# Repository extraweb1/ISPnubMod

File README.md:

# ISPnubMod

Firmware for stand-alone AVR programmer module.

ISPnub is a stand-alone AVR programming module. The programming instructions
are defined within scripts. These scripts are converted with an additional
tool (ISPnubCreator) into a binary format and are stored in the flash of
ISPnub's ATmega1284P. This firmware interprets the binary programming
instructions and executes it on the connected target controller.
 
The firmware hex file is packed into the JAR file of ISPnubCreator which
merges the firmware hex data with programming instructions from scripts.

## Hardware / Boards

There are two dedicated boards to build the ISPnub. The original board is very small, further information you can get at the inventor of the <a href="http://www.fischl.de/ispnub/">original ISPnub</a>. The modded board <a href="https://oshpark.com/shared_projects/0ZfQJilI">can be ordered e.g. from OSHpark</a> and has some extra features on it:
  * Supported AVRs: ATmega1284, ATmega644, ATmega328@16MHz (Arduino Uno), ATmega32/16 (still untested)
  * 2 Power-Connectors
  * Buzzer
  * Connector for ISP 6-Header, Clamp and DIP-Socket
  * Internal vias for connecting a custom ISP-Header
  * Yellow LED for active programming state so the red one is used exclusively to display errors
  * Possibility to add a power switch (or just use a jumper)
  * 2 PINs breaked out for additional auxiliaries
Eagle files like schematics are to be found in 

If you would like to test the system on Arduino Uno first here is a connection diagram. Please be aware that the ISPnub-software only works if flashing the Arduino via ISP directly omitting the bootloader.

## Set up the Software / Usage

Detailed explanation about function and usage of the ISPnub are to be found at <a href="http://www.fischl.de/ispnub/">fischl.de</a>

In short:

### 1. Write a programming script (test.ispnub):
```
CONNECT 2000000                           ; connect with SCK = 2 MHz 
SPIVERIFY 0x30, 0x00, 0x00, 0x00, 0x1E    ; check signature byte 0x00 (0x1E = manufactured by Atmel)
SPIVERIFY 0x30, 0x00, 0x01, 0x00, 0x93    ; check signature byte 0x01 (0x93 = 8KB Flash memory)
SPIVERIFY 0x30, 0x00, 0x02, 0x00, 0x07    ; check signature byte 0x02 (0x07 = ATmega8 device)
SPIWRITE  0xAC, 0x80, 0x00, 0x00          ; chip erase
WAIT 2                                    ; wait 20 ms
FLASH ../test/main.hex, 0, 64             ; flash given hex file starting at flash address 0 with pagesize 64
DISCONNECT                                ; disconnect SPI
DECCOUNTER 10                             ; allow 10 programming cycles
END
```
### 2. Build ISPnub firmware:
Take the java tool  to build the firmware to be flashed to the ISPnub/Arduino.
Build the firmware like this for Arduino:
```
java -jar ISPnubCreator.jar test.ispnub atmega328_16MHz ispnub.hex
```

To use the modded firmware in compatibility-mode on the original ISPnub board execute:
```
java -jar ISPnubCreator.jar test.ispnub atmega1284_compat ispnub.hex
```

Or choose one of the other supported AVR in combination with the modded board:
```
java -jar ISPnubCreator.jar test.ispnub [atmega1284|atmega1284_compat|atmega328_16MHz|atmega16|atmega32|atmega644] ispnub.hex
```

### 3. Flash the ISPnub/Arduino:
Now the generated "ispnub.hex" can be flashed with your favorite programmer into the arduino. Take care for setting the fuses right. A working suggestion is given on the commandline by the java tool after building the firmware in step 2.

### 4. Flash targets by hitting the switch on the ISPnub

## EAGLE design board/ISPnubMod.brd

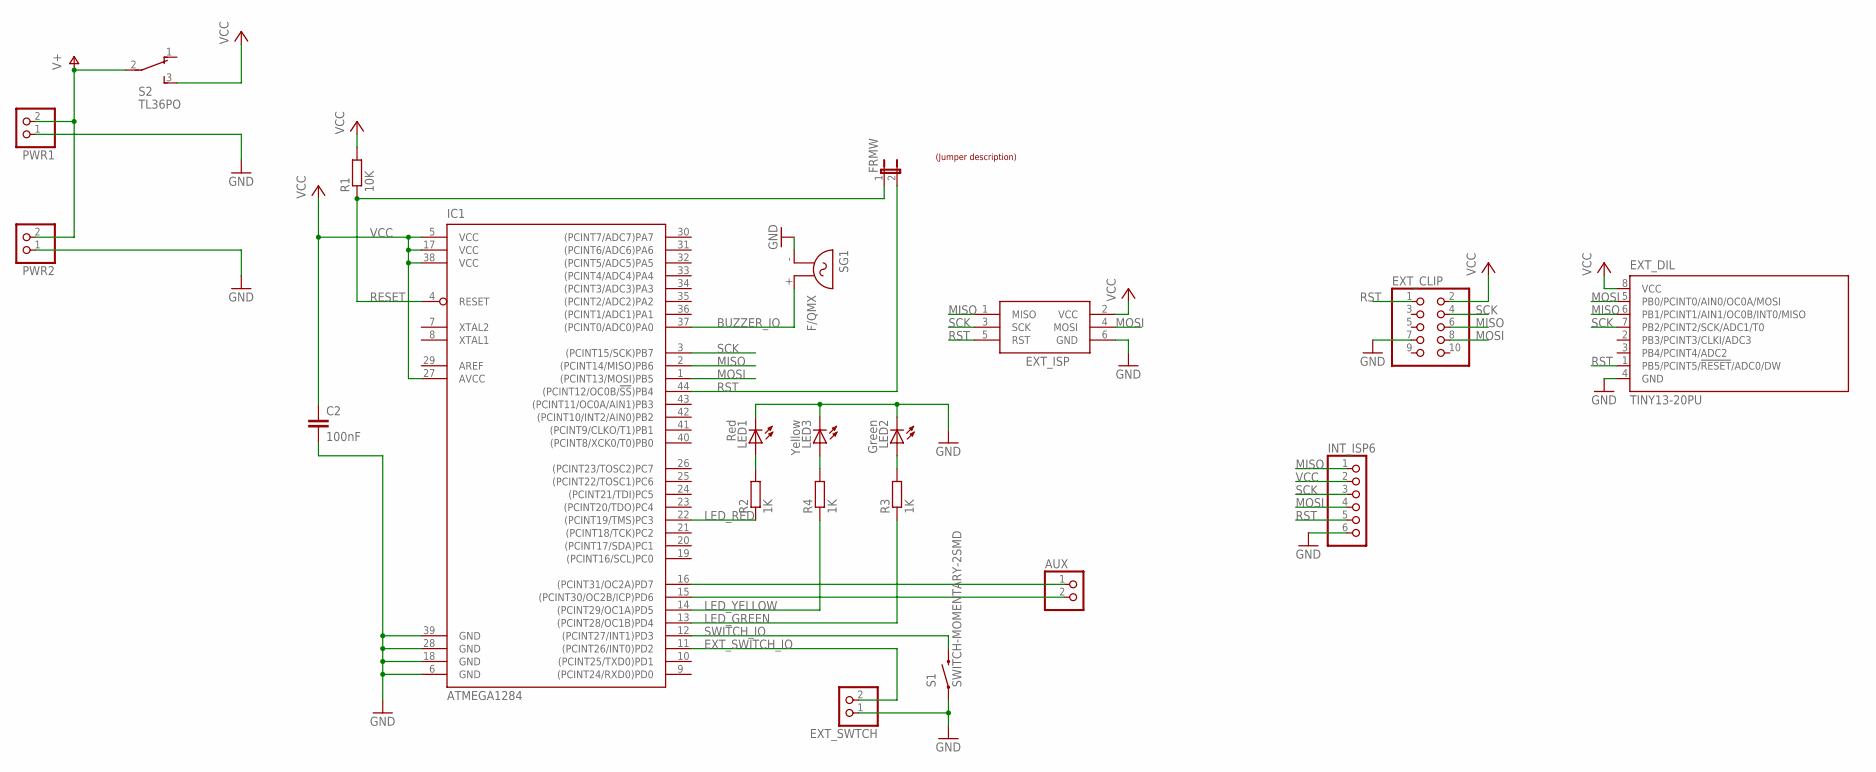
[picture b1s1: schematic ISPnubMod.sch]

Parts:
AUX: PINHD-1X2; 1X02
C2: 100nF; C0805; MOUSER# 80-C0805C104K5R
EXT_CLIP: PINHD-2X5; 2X05
EXT_DIL: TINY13-20PU; DIL08
EXT_ISP: AVRISP-6; AVRISP
EXT_SWTCH: PINHD-1X2; 1X02
FRMW: JP1E; JP1; MOUSER# 571-826936-2
IC1: ATMEGA1284; TQFP44; MOUSER# 556-ATMEGA1284P-AU
INT_ISP6: PINHD-1X6; 1X06
LED1: Red; CHIP-LED0805; MOUSER# 604-APT1608SURC
LED2: Green; CHIP-LED0805; MOUSER# 604-APT2012SGC
LED3: Yellow; CHIP-LED0805; MOUSER# 604-APT2012SGC
PWR1, PWR2: PINHD-1X2; 1X02
R1: 10K; R0805; MOUSER# 603-SR0805JR-0710KL
R2, R3, R4: 1K; R0805; MOUSER# 71-CRCW0805-1.0K-E3
S1: SWITCH-MOMENTARY-2SMD; TACTILE_SWITCH_SMD; MOUSER# 693-1301.9314
S2: TL36PO; TL3XPO
SG1: F/QMX
U$1: LABEL_JUMPER_1X2; JUMP2_DESC

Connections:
BUZZER_IO: IC1.37 ((PCINT0/ADC0)PA0), SG1.+ (2)
EXT_SWITCH_IO: EXT_SWTCH.2, IC1.11 ((PCINT26/INT0)PD2)
GND: C2.2, EXT_CLIP.7, EXT_DIL.4 (GND), EXT_ISP.6 (GND), EXT_SWTCH.1, IC1.6 (GND), IC1.18 (GND), IC1.28 (GND), IC1.39 (GND), INT_ISP6.6, LED1.C, LED2.C, LED3.C, PWR1.1, PWR2.1, S1.1, SG1.- (1)
LED_GREEN: IC1.13 ((PCINT28/OC1B)PD4), R3.1
LED_RED: IC1.22 ((PCINT19/TMS)PC3), R2.1
LED_YELLOW: IC1.14 ((PCINT29/OC1A)PD5), R4.1
MISO: EXT_CLIP.6, EXT_DIL.6 (PB1/PCINT1/AIN1/OC0B/INT0/MISO), EXT_ISP.1 (MISO), IC1.2 ((PCINT14/MISO)PB6), INT_ISP6.1
MOSI: EXT_CLIP.8, EXT_DIL.5 (PB0/PCINT0/AIN0/OC0A/MOSI), EXT_ISP.4 (MOSI), IC1.1 ((PCINT13/MOSI)PB5), INT_ISP6.4
unnamed: LED1.A, R2.2
unnamed: LED2.A, R3.2
unnamed: LED3.A, R4.2
PD6: AUX.2, IC1.15 ((PCINT30/OC2B/ICP)PD6)
PD7: AUX.1, IC1.16 ((PCINT31/OC2A)PD7)
RESET: FRMW.1, IC1.4 (RESET), R1.1
RST: EXT_CLIP.1, EXT_DIL.1 (PB5/PCINT5/!RESET!/ADC0/DW), EXT_ISP.5 (RST), FRMW.2, IC1.44 ((PCINT12/OC0B/!SS!)PB4), INT_ISP6.5
SCK: EXT_CLIP.4, EXT_DIL.7 (PB2/PCINT2/SCK/ADC1/T0), EXT_ISP.3 (SCK), IC1.3 ((PCINT15/SCK)PB7), INT_ISP6.3
SWITCH_IO: IC1.12 ((PCINT27/INT1)PD3), S1.3 (2)
V+: PWR1.2, PWR2.2, S2.2
VCC: C2.1, EXT_CLIP.2, EXT_DIL.8 (VCC), EXT_ISP.2 (VCC), IC1.5 (VCC), IC1.17 (VCC), IC1.27 (AVCC), IC1.38 (VCC), INT_ISP6.2, R1.2, S2.3 (S)

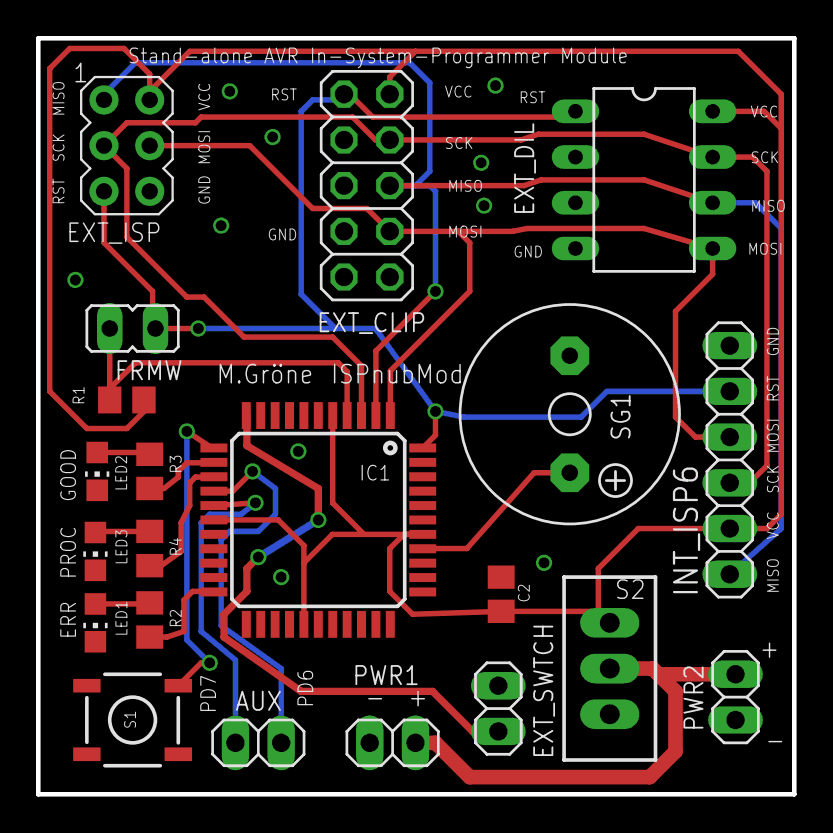
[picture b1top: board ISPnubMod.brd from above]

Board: 2 copper layers, 42.0 x 42.0 mm, 22 parts (1 on the bottom side), 19 nets.

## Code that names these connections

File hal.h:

/**
 * @file hal.h
 *
 * @brief This file contains definitions for hardware abstraction
 *
 * @author Thomas Fischl, Michael Gröne
 * @copyright (c) 2013, 2017 Thomas Fischl, Michael Gröne
 * 
 * This program is free software: you can redistribute it and/or modify
 * it under the terms of the GNU General Public License as published by
 * the Free Software Foundation, either version 3 of the License, or
 * (at your option) any later version.
 * 
 * This program is distributed in the hope that it will be useful,
 * but WITHOUT ANY WARRANTY; without even the implied warranty of
 * MERCHANTABILITY or FITNESS FOR A PARTICULAR PURPOSE. See the
 * GNU General Public License for more details.
 * 
 * You should have received a copy of the GNU General Public License
 * along with this program. If not, see <http://www.gnu.org/licenses/>.
 * 
 */

#ifndef _HAL_
#define _HAL_


#if defined (__AVR_ATmega16__) || defined (__AVR_ATmega16A__) || defined (__AVR_ATmega32__)
	//#define TCCR0 TCCR0	__-> are as is
	//#define TIMSK TIMSK	
	#define INT_MSK GICR
	#define HAS_DYNAMIC_BOD_CONTROL 0
#else
	#define TCCR0 TCCR0B
	#define TIMSK TIMSK0
	#define INT_MSK EIMSK
	#define HAS_DYNAMIC_BOD_CONTROL 1
#endif

// ******************************** ATmega1284(P) / ATmega16(A) / ATmega32 / ATmega644(A/P) *******************************
#if defined (__AVR_ATmega1284__) || defined (__AVR_ATmega1284P__) || defined (__AVR_ATmega16__) || defined (__AVR_ATmega16A__) || defined (__AVR_ATmega32__) || defined (__AVR_ATmega644__) || defined (__AVR_ATmega644A__) || defined (__AVR_ATmega644P__)

	// all have to run at 8MHz internal clock

	#define IO_LED_GREEN	PD4		// at Port D
	#define IO_LED_YELLOW	PD5		// at Port D
	#define IO_LED_RED		PC3		// at Port C
	#define IO_BUZZER		PA0		// at Port A
	#define IO_SWITCH		PD3		// at Port D (INT1)
	#define IO_EXT_SWITCH	PD2		// at Port D (INT0)
	#define IO_SWITCH_PIN	PIND	// all switches have to be on same port to be debounced

	#if COMPATIBILITY_MODE_ISPNUB_ORIGINAL == 1
		//inverted logic on ISPnub Original
		#define hal_setLEDgreen(x)	PORTD =	(PORTD & ~(1 << IO_LED_GREEN))	| ((!x) << IO_LED_GREEN)
		#define hal_setLEDyellow(x)	PORTD =	(PORTD & ~(1 << IO_LED_YELLOW))	| ((!x) << IO_LED_YELLOW)
		#define hal_setLEDred(x)	PORTC =	(PORTC & ~(1 << IO_LED_RED))	| ((!x) << IO_LED_RED)
	#else
		//active low on ISPnubMod
		#define hal_setLEDgreen(x)	PORTD =	(PORTD & ~(1 << IO_LED_GREEN))	| ((x) << IO_LED_GREEN)
		#define hal_setLEDyellow(x)	PORTD =	(PORTD & ~(1 << IO_LED_YELLOW))	| ((x) << IO_LED_YELLOW)
		#define hal_setLEDred(x)	PORTC =	(PORTC & ~(1 << IO_LED_RED))	| ((x) << IO_LED_RED)
	#endif

	#define hal_setBuzzer(x)	PORTA = (PORTA & ~(1 << IO_BUZZER))		| ((x) << IO_BUZZER)
	#define hal_init()			DDRD = (1 << IO_LED_GREEN) | (1 << IO_LED_YELLOW); DDRC = (1 << IO_LED_RED); DDRA = (1 << IO_BUZZER); PORTD = ( (1<<IO_SWITCH) | (1<<IO_EXT_SWITCH) );	//LEDs & Buzzer: Output; Switch: Enable Pullup
	#define hal_enableINT0()	INT_MSK |= (1<<INT0);												//Enable INT0, fire on low level (this is the only detectable state in powerdown)
	#define hal_disableINT0()	INT_MSK &= ~(1<<INT0);
	#define hal_enableINT1()	INT_MSK |= (1<<INT1);												//Enable INT1, fire on low level (this is the only detectable state in powerdown)
	#define hal_disableINT1()	INT_MSK &= ~(1<<INT1);

	#define	ISP_OUT   PORTB
	#define ISP_IN    PINB
	#define ISP_DDR   DDRB
	#define ISP_RST   PB4
	#define ISP_MOSI  PB5
	#define ISP_MISO  PB6
	#define ISP_SCK   PB7

// ************************ ATmega328@16MHz in Arduino Uno *****************************
#elif defined (__AVR_ATmega328P__) || defined (__AVR_ATmega328__)

	// Arduino Uno has 16MHz Crystal -> scaled by 2 to have correct timing.
	// Attention: Firmware works only if flashed via ISP (without bootloader) onto Arduino.

	#if COMPATIBILITY_MODE_ISPNUB_ORIGINAL == 1
		#error COMPATIBILITY_MODE not supported for ATmega328
	#endif

	#define IO_LED_GREEN	PC3		// Arduino Uno: A3
	#define IO_LED_YELLOW	PC2		// Arduino Uno: A2
	#define IO_LED_RED		PC1		// Arduino Uno: A1
	#define IO_BUZZER		PC0		// Arduino Uno: A0
	#define IO_SWITCH		PD3		// Arduino Uno: D3 (INT1)
	#define IO_EXT_SWITCH	PD2		// Arduino Uno: D2 (INT0)
	#define IO_SWITCH_PIN	PIND	// all switches have to be on same port to be debounced

	#define hal_setLEDgreen(x)	PORTC =	(PORTC & ~(1 << IO_LED_GREEN))	| ((x) << IO_LED_GREEN)
	#define hal_setLEDyellow(x)	PORTC =	(PORTC & ~(1 << IO_LED_YELLOW))	| ((x) << IO_LED_YELLOW)
	#define hal_setLEDred(x)	PORTC =	(PORTC & ~(1 << IO_LED_RED))	| ((x) << IO_LED_RED)
	#define hal_setBuzzer(x)	PORTC = (PORTC & ~(1 << IO_BUZZER))		| ((x) << IO_BUZZER)
	#define hal_init()			clock_prescale_set(2); DDRC = ( (1 << IO_LED_GREEN) | (1 << IO_LED_YELLOW) | (1 << IO_LED_RED) | (1 << IO_BUZZER) ); PORTD = ( (1<<IO_SWITCH) | (1<<IO_EXT_SWITCH) );	//LEDs & Buzzer: Output; Switch: Enable Pullup
	#define hal_enableINT0()	INT_MSK |= (1<<INT0);												//Enable INT0, fire on low level (this is the only detectable state in powerdown)
	#define hal_disableINT0()	INT_MSK &= ~(1<<INT0);
	#define hal_enableINT1()	INT_MSK |= (1<<INT1);												//Enable INT1, fire on low level (this is the only detectable state in powerdown)
	#define hal_disableINT1()	INT_MSK &= ~(1<<INT1);

	#define	ISP_OUT   PORTB
	#define ISP_IN    PINB
	#define ISP_DDR   DDRB
	#define ISP_RST   PB2		// Arduino Uno: D10
	#define ISP_MOSI  PB3		// Arduino Uno: D11
	#define ISP_MISO  PB4		// Arduino Uno: D12
	#define ISP_SCK   PB5		// Arduino Uno: D13


// ****************************** unknown device *********************************
#else 
  #error "MCU not supported by HAL"
#endif


#if defined (__AVR_ATmega1284__) || defined (__AVR_ATmega1284P__)
	//for AVR with flash > 64kb
	#define DEFINE_DATAPOINTER uint32_t scriptdata_p = FAR(scriptdata);
	#define flash_readbyte(x) pgm_read_byte_far(x)
#else
	//for AVR with flash < 64kb
	#define DEFINE_DATAPOINTER uint16_t scriptdata_p = (uint16_t)scriptdata
	#define flash_readbyte(x) pgm_read_byte(x)
#endif


/**
 * @brief Macro to access strings defined in PROGMEM above 64kB
 */
#define FAR(var)                     \
({ uint_farptr_t tmp;                \
   __asm__ __volatile__(             \
       "ldi    %A0, lo8(%1)"  "\n\t" \
       "ldi    %B0, hi8(%1)"  "\n\t" \
       "ldi    %C0, hh8(%1)"  "\n\t" \
       : "=d" (tmp)                  \
       : "p"  (&(var)));             \
   tmp;                              \
})

#endif

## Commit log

2017-01-31 +debounce routine +state machine
2017-01-31 fixed compile errs
2017-01-31 +enable/disable INT0/1 level-interrupt not to be flooded if button is hold +run_script currently substituted by debug-dummy +fixed ticker10MS +correct calling syntax for get_key_press
2017-02-01 +simple NO_PROGRAM-detection (if ISPnub Creator was not used)
2017-02-02 +hal for Arduino Uno +goto sleep even in S_NO_MORE and S_NO_PROGRAM
2017-02-02 updated version info fixed goto sleep
2017-02-02 +hal.h clockscale for arduino uno -bootloader and firmware offsets in memory have to be respected -> needs to be fixed -fixed immediate sleep after sleep
2017-02-03 -compatibility-break with ISPnub board -updated HAL to add more AVRs -yellow led added
2017-02-03 fixed buzzing
2017-02-03 shorter buzzer times
2017-02-03 +media
2017-02-05 added eagle-files
2017-02-17 +notice
2017-02-17 fixed falling asleep after long-lasting programming task
2017-02-18 fixed hal.h added main.h prep for compatibility mode
2017-02-25 hal: format and compat mode for ISPnub original main: signaling script.c: inline-scripts for debugging purpose
2017-02-26 fixed hal for atmega16/32 arduino circuitry
2017-02-26 update board-pic
2017-02-26 update pic
2017-03-03 first testing-routines
2017-03-05 +added first routines for automated testing
